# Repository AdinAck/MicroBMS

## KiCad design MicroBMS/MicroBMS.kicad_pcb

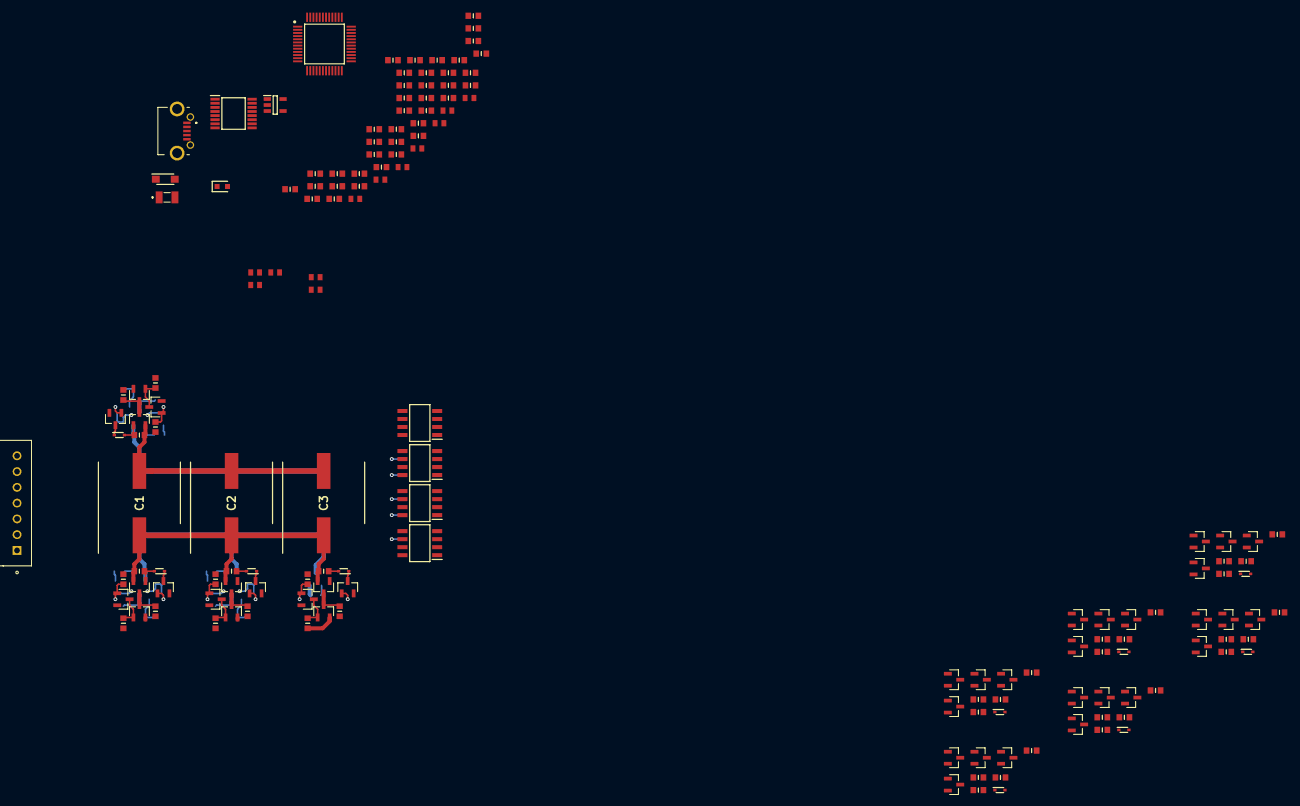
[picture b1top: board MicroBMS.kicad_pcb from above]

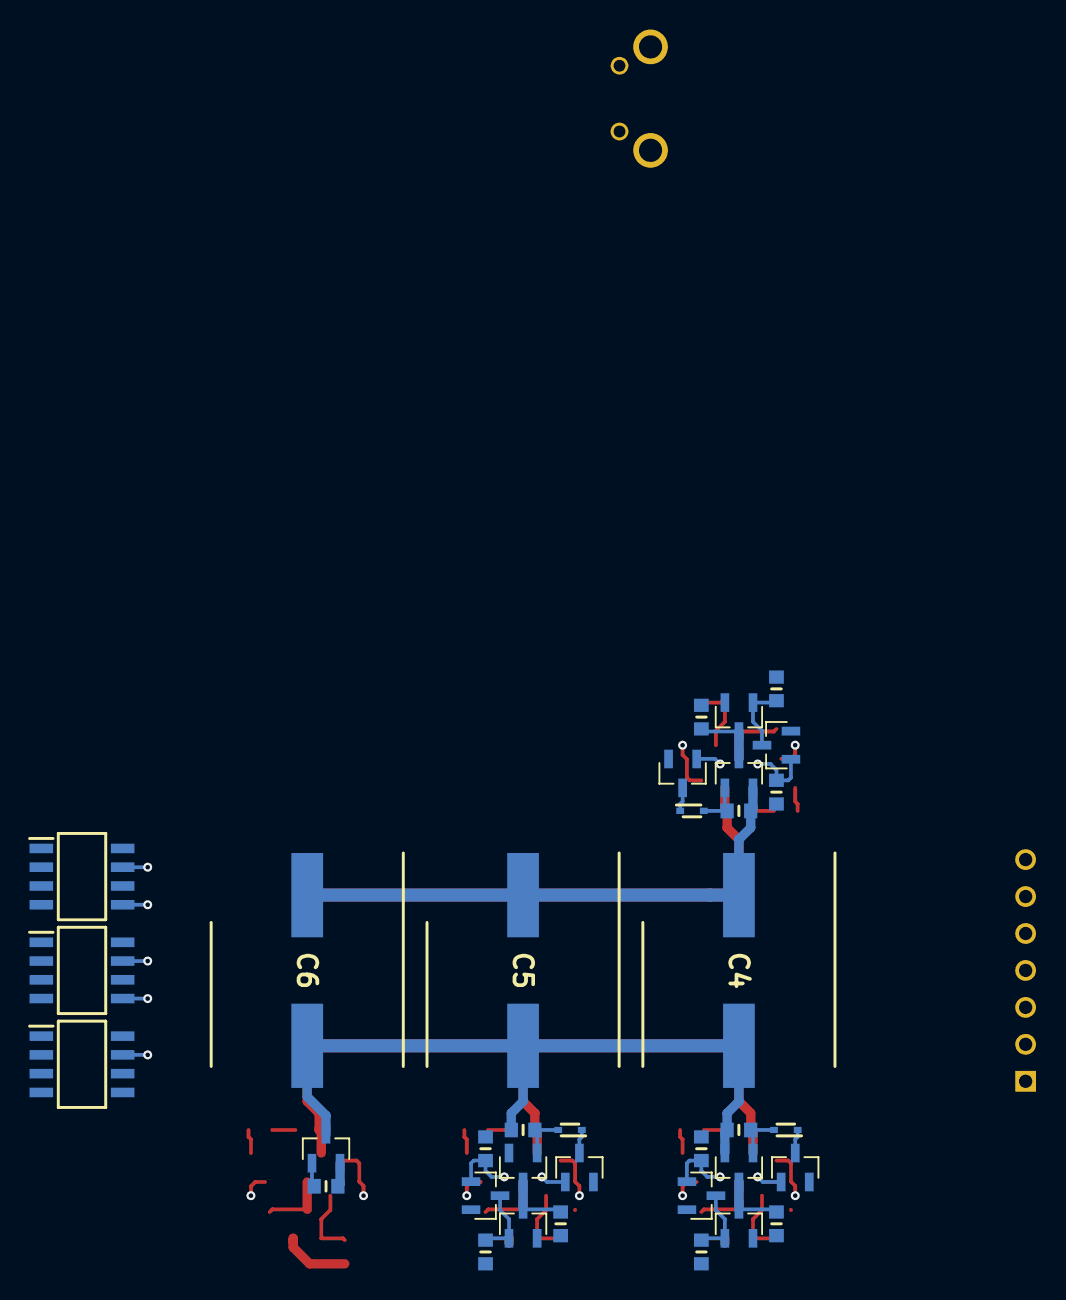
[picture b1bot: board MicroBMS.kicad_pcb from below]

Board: 4 copper layers, 191 parts (35 on the bottom side), 121 nets.

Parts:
C1, C2, C3, C4, C5, C6: 25TRV1000M12.5X13.5; CAPAE1300X1400N
C7, C9, C13, C16, C18: 06033C104KAT2A; CAPC1608X90N
C8, C10: 0603ZD106KAT2A; CAPC1608X90N
C11, C15: 06035A220JAT4A; CAPC1608X90N
C12, C14, C17: 0603ZC105KAT2A; CAPC1608X90N
D1: MBR120VLSFT3G; SODFL3616X98N
D2, D3, D4, D5, D6, D7, D8, D9, D10, D11, D12, D13, D14: BAP50-02,115; SODFL1608X65N
IC1, IC2, IC3, IC4, IC5, IC6, IC7: LTV-207; SOIC127P610X363-8N
IC8: MAX4617CUE+; SOP65P640X110-16N
IC9: SPX3819M5-L-3-3_TR; SOT95P280X145-5N
IC10: ATSAMD21G18A-AU; QFP50P900X900X120-48N
J1: UJ2-MIBH2-4-SMT-TR; UJ2MIBH24SMTTR
LED1: APT1608LSECK_J3-PRV; APT1608CGCK
P1: S7B-XH-A(LF)(SN); JST_S7B-XH-A(LF)(SN)
Q1, Q4, Q5, Q8, Q9, Q12, Q13, Q16, Q17, Q20, Q21, Q24, Q25, Q28, Q29, Q32, Q33, Q36, Q37, Q40, Q41, Q44, Q45, Q48, Q49, Q52, Q53: PMV90ENE; SOT95P230X110-3N
Q2, Q3, Q6, Q7, Q10, Q11, Q14, Q15, Q18, Q19, Q22, Q23, Q26, Q27, Q30, Q31, Q34, Q35, Q38, Q39, Q42, Q43, Q46, Q47, Q50, Q51: PMV74EPE; SOT95P230X110-3N
R1, R41, R43, R44, R45, R47, R48, R49, R51, R52, R53, R55, R56, R57, R59, R60, R61, R63, R64, R65, R67, R68, R69, R71, R72, R73, R75, R76, R77, R79, R80, R81, R83, R84, R85, R87, R88, R89, R91, R92: ERJ-3GEYJ203V; RESC1608X55N
R2, R4, R8, R11, R12, R15, R16, R17, R21, R22, R24, R27, R28, R33: RT0603BRD0750KL; RESC1608X55N
R3, R5, R6, R7, R9, R10, R13, R14, R18, R19, R20, R23, R25, R26, R29, R30, R31, R32, R35, R36, R42, R46, R50, R54, R58, R62, R66, R70, R74, R78, R82, R86, R90: ERJ-3EKF1003V; RESC1608X55N
R34: ERJ-3GEYJ301V; RESC1608X55N
R37, R38, R39: ERJ-3GEYJ472V; RESC1608X55N
R40: ERJ-3EKF7500V; RESC1608X55N
Y1: ABS07-166-32.768KHZ-T; ABS0716632768KHZT

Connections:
3v3: C9.1, C10.1, C12.1, C13.1, C16.1, C18.1, IC8.16, IC9.5, IC10.6, IC10.17, IC10.36, IC10.44, R34.2
/Switch1/Vc: IC7.7, Q4.1, Q5.1, R44.1
/Switch2/Vc: IC6.5, Q8.1, Q9.1, R48.1
/Switch3/Vc: IC6.7, Q12.1, Q13.1, R52.1
/Switch4/Vc: IC5.5, Q16.1, Q17.1, R56.1
/Switch5/Vc: IC5.7, Q32.1, Q33.1, R72.1
/Switch6/Vc: IC4.5, Q28.1, Q29.1, R68.1
/Switch7/Vc: IC4.7, Q24.1, Q25.1, R64.1
/Switch8/Vc: IC3.5, Q20.1, Q21.1, R60.1
/Switch9/Vc: IC3.7, Q36.1, Q37.1, R76.1
/Switch10/Vc: IC2.5, Q40.1, Q41.1, R80.1
/Switch11/Vc: IC2.7, Q44.1, Q45.1, R84.1
/Switch12/Vc: IC1.5, Q48.1, Q49.1, R88.1
/Switch13/Vc: IC1.7, Q52.1, Q53.1, R92.1
A: IC10.25, R37.2
B: IC10.27, R38.2
C: IC10.28, R39.2
C1: IC7.1, IC7.3, IC8.13
C2: IC6.1, IC6.3, IC8.14
C3: IC5.1, IC5.3, IC8.15
C4: IC4.1, IC4.3, IC8.12
C5: IC3.1, IC3.3, IC8.1
C6: IC2.1, IC2.3, IC8.5
C7: IC1.1, IC1.3, IC8.2
Cap+: C1.1, C2.1, C3.1, C4.1, C5.1, C6.1, Q3.2, Q11.2, Q23.2, Q31.2, Q35.2, Q43.2, Q51.2, R43.2, R51.2, R63.2, R71.2, R75.2, R83.2, R91.2
Cap-: C1.2, C2.2, C3.2, C4.2, C5.2, C6.2, Q1.3, Q7.2, Q15.2, Q19.2, Q27.2, Q39.2, Q47.2, R47.2, R55.2, R59.2, R67.2, R79.2, R87.2
Cell1: IC6.6, IC7.6, IC7.8, P1.2, Q2.2, Q6.2, Q12.2, Q13.2, Q16.2, Q17.2, R2.1, R41.2, R45.2, R52.2, R56.2
Cell1S: IC10.3, R2.2, R3.1
Cell2: D1.2, IC5.6, IC6.8, P1.3, Q10.2, Q14.2, Q28.2, Q29.2, Q32.2, Q33.2, R6.1, R49.2, R53.2, R68.2, R72.2
Cell2S: IC10.7, R4.2, R5.1
Cell3: IC4.6, IC5.8, P1.4, Q20.2, Q21.2, Q24.2, Q25.2, Q26.2, Q30.2, R10.1, R60.2, R64.2, R65.2, R69.2
Cell3S: IC10.8, R8.2, R9.1
Cell4: IC3.6, IC4.8, P1.5, Q18.2, Q22.2, Q36.2, Q37.2, Q40.2, Q41.2, R14.1, R57.2, R61.2, R76.2, R80.2
Cell4S: IC10.9, R12.2, R13.1
Cell5: IC2.6, IC3.8, P1.6, Q34.2, Q38.2, Q44.2, Q45.2, Q48.2, Q49.2, R19.1, R73.2, R77.2, R84.2, R88.2
Cell5S: IC10.10, R17.2, R18.1
Cell6: IC1.6, IC2.8, P1.7, Q42.2, Q46.2, Q52.2, Q53.2, R24.1, R81.2, R85.2, R92.2
Cell6S: IC10.12, R22.2, R23.1
Cell7: IC1.8, Q50.2, R30.1, R89.2
Cell7S: IC10.47, R28.2, R29.1
D+: IC10.34, J1.2
D-: IC10.33, J1.3
GNDREF: C7.2, C8.2, C9.2, C10.2, C11.2, C12.2, C13.2, C14.2, C15.2, C16.2, C17.2, C18.2, IC1.2, IC1.4, IC2.2, IC2.4, IC3.2, IC3.4, IC4.2, IC4.4, IC5.2, IC5.4, IC6.2, IC6.4, IC7.2, IC7.4, IC8.8, IC10.5, IC10.18, IC10.35, IC10.42, J1.5, J1.MH1, J1.MH2, J1.MH3, J1.MH4, LED1.1, P1.1, Q1.2, Q4.2, Q5.2, Q8.2, Q9.2, R1.1, R3.2, R5.2, R7.2, R9.2, R11.2, R13.2, R16.2, R18.2, R21.2, R23.2, R27.2, R29.2, R33.2, R35.2, R42.2, R44.2, R46.2, R48.2, R50.2, R54.2, R58.2, R62.2, R66.2, R70.2, R74.2, R78.2, R82.2, R86.2, R90.2
unnamed: C7.1, IC8.3, R34.1
unnamed: C11.1, IC10.2, Y1.1
unnamed: C14.1, IC10.4
unnamed: C15.1, IC10.1, Y1.2
unnamed: C17.1, IC10.43
unnamed: D2.1, Q4.3
unnamed: D2.2, Q3.1, R43.1
unnamed: D3.1, Q8.3
unnamed: D3.2, Q7.1, R47.1
unnamed: D4.1, Q12.3
unnamed: D4.2, Q11.1, R51.1
unnamed: D5.1, Q16.3
unnamed: D5.2, Q15.1, R55.1
unnamed: D6.1, Q20.3
unnamed: D6.2, Q19.1, R59.1
unnamed: D7.1, Q24.3
unnamed: D7.2, Q23.1, R63.1
unnamed: D8.1, Q28.3
unnamed: D8.2, Q27.1, R67.1
unnamed: D9.1, Q32.3
unnamed: D9.2, Q31.1, R71.1
unnamed: D10.1, Q36.3
unnamed: D10.2, Q35.1, R75.1
unnamed: D11.1, Q40.3
unnamed: D11.2, Q39.1, R79.1
unnamed: D12.1, Q44.3
unnamed: D12.2, Q43.1, R83.1
unnamed: D13.1, Q48.3
unnamed: D13.2, Q47.1, R87.1
unnamed: D14.1, Q52.3
unnamed: D14.2, Q51.1, R91.1
unnamed: IC7.5, Q1.1, R1.2
unnamed: IC8.4, R35.1
unnamed: IC8.9, R39.1
unnamed: IC8.10, R38.1
unnamed: IC8.11, R37.1
unnamed: IC9.3, R36.2
unnamed: IC10.26, R40.1
unnamed: LED1.2, R40.2
unnamed: Q2.1, Q5.3, R41.1
unnamed: Q2.3, Q3.3, R42.1
unnamed: Q6.1, Q9.3, R45.1
unnamed: Q6.3, Q7.3, R46.1
unnamed: Q10.1, Q13.3, R49.1
unnamed: Q10.3, Q11.3, R50.1
unnamed: Q14.1, Q17.3, R53.1
unnamed: Q14.3, Q15.3, R54.1
unnamed: Q18.1, Q21.3, R57.1
unnamed: Q18.3, Q19.3, R58.1
unnamed: Q22.1, Q25.3, R61.1
unnamed: Q22.3, Q23.3, R62.1
unnamed: Q26.1, Q29.3, R65.1
unnamed: Q26.3, Q27.3, R66.1
unnamed: Q30.1, Q33.3, R69.1
unnamed: Q30.3, Q31.3, R70.1
unnamed: Q34.1, Q37.3, R73.1
unnamed: Q34.3, Q35.3, R74.1
unnamed: Q38.1, Q41.3, R77.1
unnamed: Q38.3, Q39.3, R78.1
unnamed: Q42.1, Q45.3, R81.1
unnamed: Q42.3, Q43.3, R82.1
unnamed: Q46.1, Q49.3, R85.1
unnamed: Q46.3, Q47.3, R86.1
unnamed: Q50.1, Q53.3, R89.1
unnamed: Q50.3, Q51.3, R90.1
unnamed: R4.1, R6.2, R7.1
unnamed: R8.1, R10.2, R11.1
unnamed: R12.1, R15.2, R16.1
unnamed: R14.2, R15.1
unnamed: R17.1, R20.2, R21.1
unnamed: R19.2, R20.1
unnamed: R22.1, R26.2, R27.1
unnamed: R24.2, R25.1
unnamed: R25.2, R26.1
unnamed: R28.1, R32.2, R33.1
unnamed: R30.2, R31.1
unnamed: R31.2, R32.1
VBUS: C8.1, D1.1, IC9.1, J1.1, R36.1
